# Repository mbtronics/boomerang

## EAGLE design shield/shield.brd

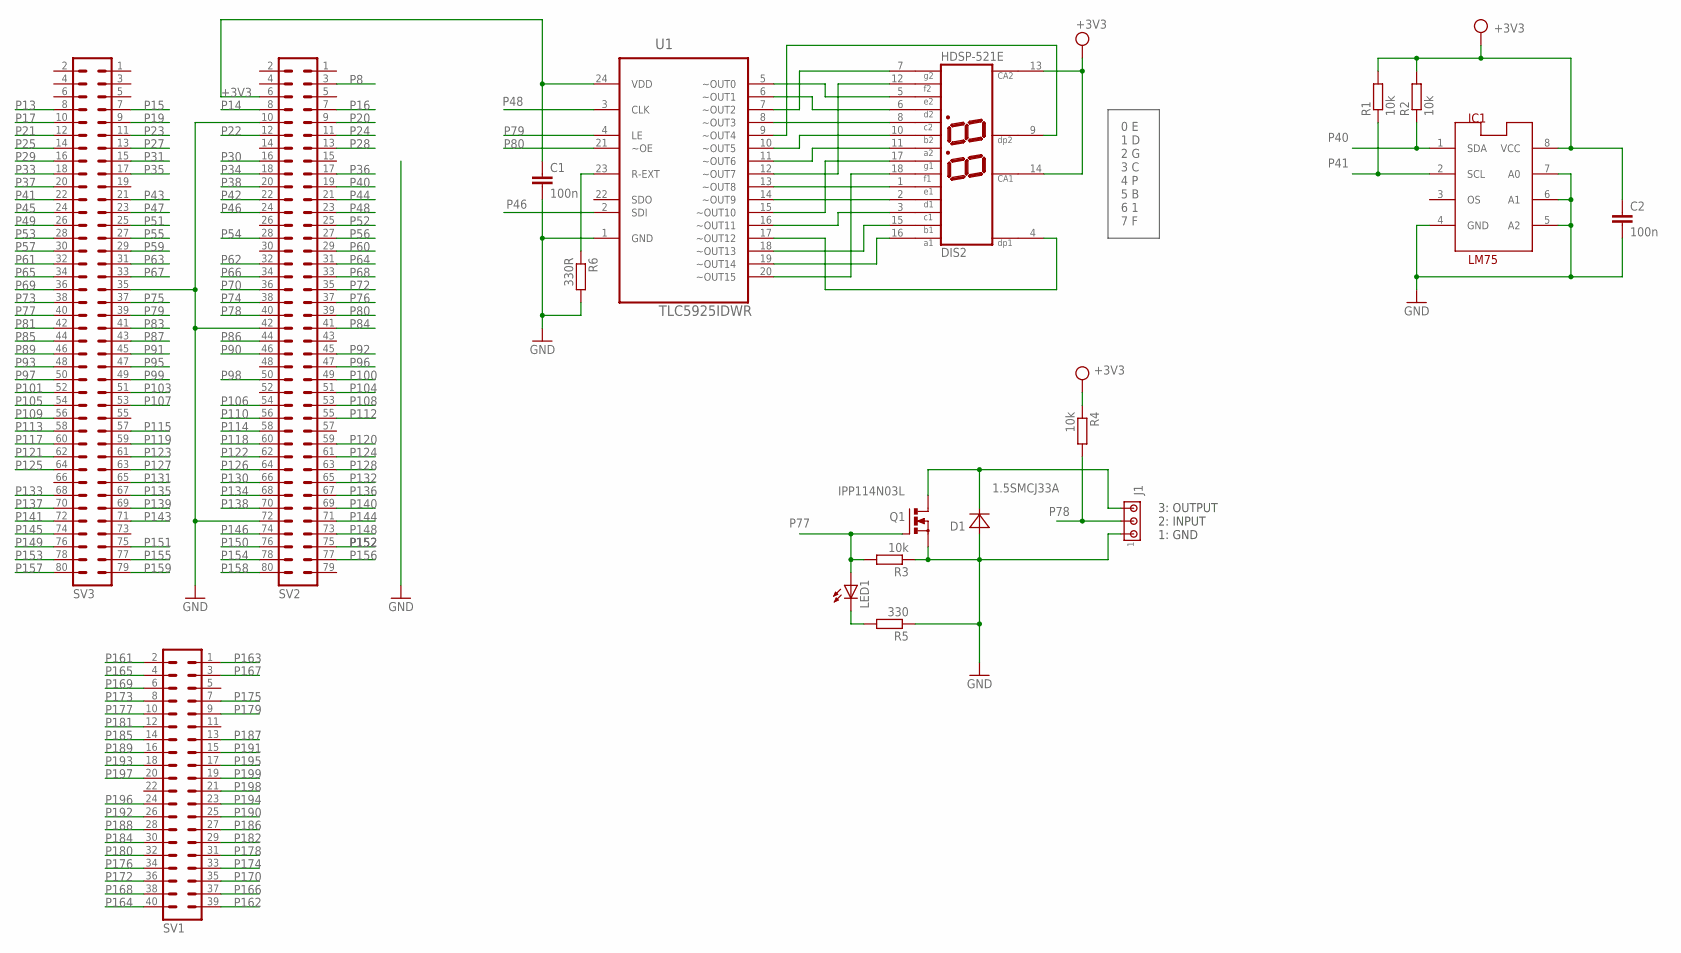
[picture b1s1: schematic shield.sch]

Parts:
C1, C2: 100n; C2.5-2
D1: 1.5SMCJ33A; DO214AB
DIS2: HDSP-521E; HDSP-R
IC1: LM75; SO8_LM75
J1: MTA03-100; 10X03MTA
LED1: LED5MM
Q1: IPP114N03L; TO220BV
R1, R2, R3, R4: 10k; 0207/10
R5: 330; 0207/10
R6: 330R; 0207/10
SV1: MA20-2
SV2, SV3: MA40-2
U1: TLC5925IDWR; SOIC127P1030X265-24N

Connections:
+3V3: C1.1, C2.1, DIS2.13 (CA2), DIS2.14 (CA1), IC1.8 (VCC), R1.2, R2.2, R4.1, SV2.6, U1.24 (VDD)
GND: C1.2, C2.2, D1.A, IC1.4 (GND), IC1.5 (A2), IC1.6 (A1), IC1.7 (A0), J1.1, Q1.S, R3.1, R5.1, R6.2, SV2.10, SV2.42, SV2.72, SV3.35, U1.1 (GND)
unnamed: DIS2.5 (E2), U1.5 (~OUT0)
unnamed: DIS2.6 (D2), U1.6 (~OUT1)
unnamed: DIS2.7 (G2), U1.7 (~OUT2)
unnamed: DIS2.8 (C2), U1.8 (~OUT3)
unnamed: DIS2.9 (DP2), U1.9 (~OUT4)
unnamed: DIS2.10 (B2), U1.10 (~OUT5)
unnamed: DIS2.11 (A2), U1.11 (~OUT6)
unnamed: DIS2.12 (F2), U1.12 (~OUT7)
unnamed: DIS2.1 (E1), U1.13 (~OUT8)
unnamed: DIS2.2 (D1), U1.14 (~OUT9)
unnamed: DIS2.17 (G1), U1.15 (~OUT10)
unnamed: DIS2.3 (C1), U1.16 (~OUT11)
unnamed: DIS2.4 (DP1), U1.17 (~OUT12)
unnamed: DIS2.15 (B1), U1.18 (~OUT13)
unnamed: DIS2.16 (A1), U1.19 (~OUT14)
unnamed: DIS2.18 (F1), U1.20 (~OUT15)
unnamed: D1.K (C), J1.3, Q1.D
unnamed: LED1.K (C), R5.2
unnamed: R6.1, U1.23 (R-EXT)
P8: SV2.3
P13: SV3.8
P14: SV2.8
P15: SV3.7
P16: SV2.7
P17: SV3.10
P19: SV3.9
P20: SV2.9
P21: SV3.12
P22: SV2.12
P23: SV3.11
P24: SV2.11
P25: SV3.14
P27: SV3.13
P28: SV2.13
P29: SV3.16
P30: SV2.16
P31: SV3.15
P33: SV3.18
P34: SV2.18
P35: SV3.17
P36: SV2.17
P37: SV3.20
P38: SV2.20
P40: IC1.1 (SDA), R2.1, SV2.19
P41: IC1.2 (SCL), R1.1, SV3.22
P42: SV2.22
P43: SV3.21
P44: SV2.21
P45: SV3.24
P46: SV2.24, U1.2 (SDI)
P47: SV3.23
P48: SV2.23, U1.3 (CLK)
P49: SV3.26
P51: SV3.25
P52: SV2.25
P53: SV3.28
P54: SV2.28
P55: SV3.27
P56: SV2.27
P57: SV3.30
P59: SV3.29
P60: SV2.29
P61: SV3.32
P62: SV2.32
P63: SV3.31
P64: SV2.31
P65: SV3.34
P66: SV2.34
P67: SV3.33
P68: SV2.33
P69: SV3.36
P70: SV2.36
P72: SV2.35
P73: SV3.38
P74: SV2.38
P75: SV3.37
P76: SV2.37
P77: LED1.A, Q1.G, R3.2, SV3.40
P78: J1.2, R4.2, SV2.40
P79: SV3.39, U1.4 (LE)
P80: SV2.39, U1.21 (~OE)
P81: SV3.42
P83: SV3.41
P84: SV2.41
P85: SV3.44
P86: SV2.44
P87: SV3.43
P89: SV3.46
P90: SV2.46
P91: SV3.45
P92: SV2.45
P93: SV3.48
P95: SV3.47
P96: SV2.47
P97: SV3.50
P98: SV2.50
P99: SV3.49
P100: SV2.49
P101: SV3.52
P103: SV3.51
P104: SV2.51
P105: SV3.54
P106: SV2.54
P107: SV3.53
P108: SV2.53
P109: SV3.56
P110: SV2.56
P112: SV2.55
P113: SV3.58
P114: SV2.58
P115: SV3.57
P117: SV3.60
P118: SV2.60
P119: SV3.59
P120: SV2.59
P121: SV3.62
P122: SV2.62
P123: SV3.61
P124: SV2.61
P125: SV3.64
P126: SV2.64
P127: SV3.63
P128: SV2.63
P130: SV2.66
P131: SV3.65
P132: SV2.65
P133: SV3.68
P134: SV2.68
P135: SV3.67
P136: SV2.67
P137: SV3.70
P138: SV2.70
P139: SV3.69
P140: SV2.69
P141: SV3.72
P143: SV3.71
P144: SV2.71
P145: SV3.74
P146: SV2.74
P148: SV2.73
P149: SV3.76
P150: SV2.76
P151: SV3.75
P152: SV2.75
P153: SV3.78
P154: SV2.78
P155: SV3.77
P156: SV2.77
P157: SV3.80
P158: SV2.80
P159: SV3.79
P161: SV1.2
P162: SV1.39
P163: SV1.1
P164: SV1.40
P165: SV1.4
P166: SV1.37
P167: SV1.3
P168: SV1.38
P169: SV1.6
P170: SV1.35
P172: SV1.36
P173: SV1.8
P174: SV1.33
P175: SV1.7
P176: SV1.34
P177: SV1.10
P178: SV1.31
P179: SV1.9
P180: SV1.32
P181: SV1.12
P182: SV1.29
P184: SV1.30
P185: SV1.14
P186: SV1.27
P187: SV1.13
P188: SV1.28
P189: SV1.16
P190: SV1.25
P191: SV1.15
P192: SV1.26
P193: SV1.18
P194: SV1.23
P195: SV1.17
P196: SV1.24
P197: SV1.20
P198: SV1.21
P199: SV1.19

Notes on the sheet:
0 E 1 D 2 G 3 C 4 P 5 B 6 1 7 F
3: OUTPUT 2: INPUT 1: GND

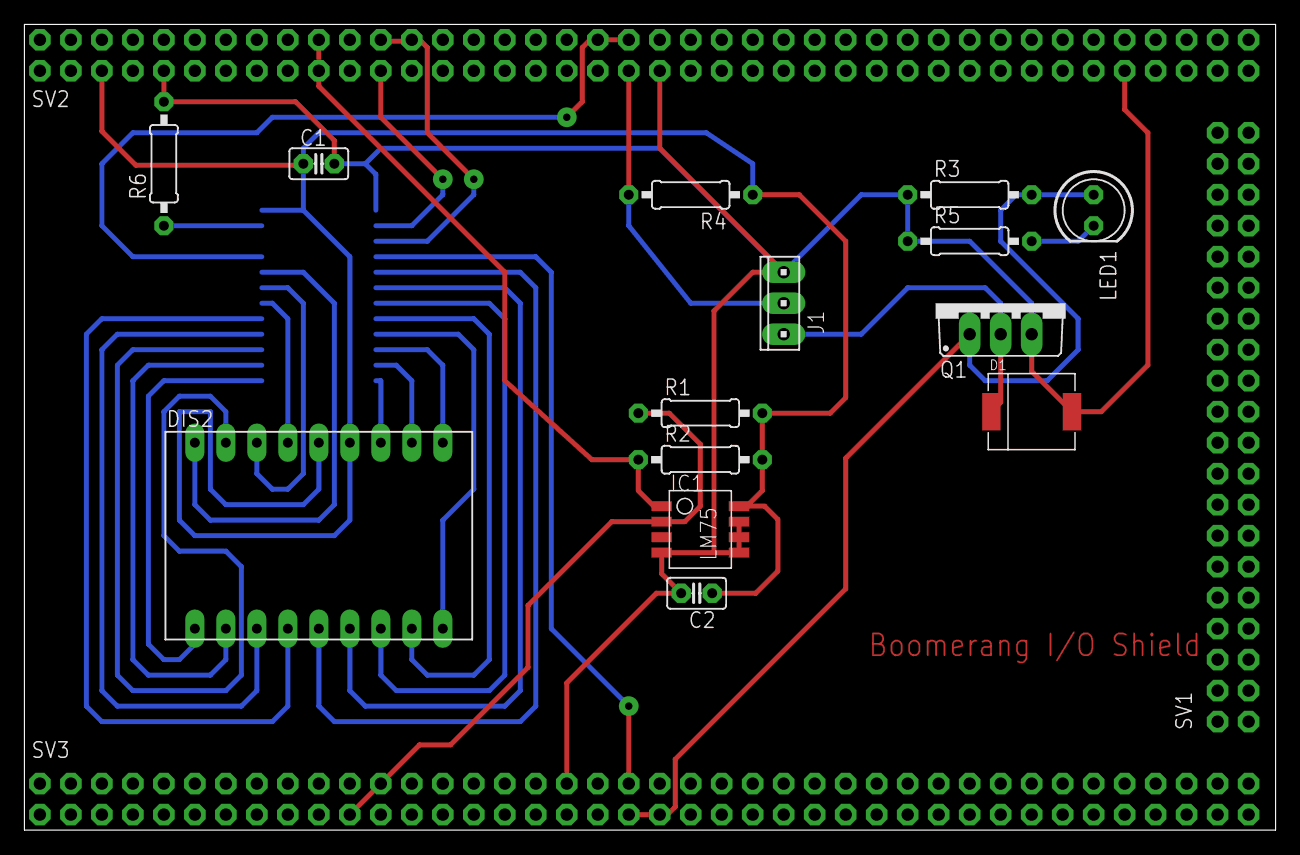
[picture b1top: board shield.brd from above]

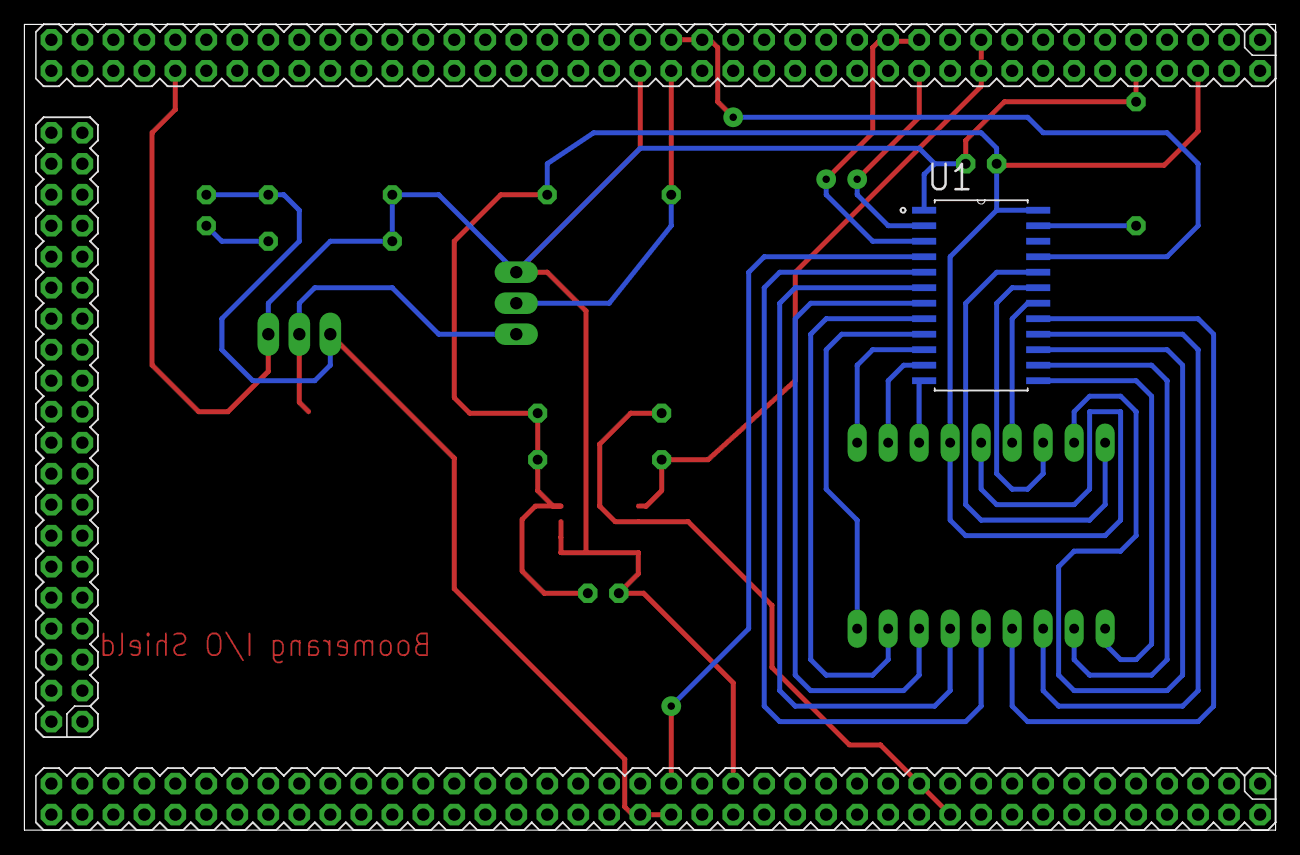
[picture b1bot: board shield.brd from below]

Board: 2 copper layers, 102.5 x 66.0 mm, 18 parts (4 on the bottom side), 29 nets.

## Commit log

2013-03-14 Add logo's
2013-03-14 Add shield library, schematic and board
2013-03-14 mv logo's
2013-03-14 add gitignore
2013-03-14 remove lm73 from shield
2013-03-25 Update schield schematic
2013-03-28 Update schematic
2013-04-24 Update schematics
2013-05-08 Update shield schematic and pcb
2013-05-12 Update board file
2013-05-12 Add capacitor
2013-05-21 update shield
2013-05-21 update shield brd
2013-05-25 Update for manufacturing
